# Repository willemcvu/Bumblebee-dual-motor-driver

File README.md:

**_NOTE: Everything here is still actively in development, and is mostly untested. Firmware has not been written; BOMs have not been created. If you'd like to use something here, I would suggest waiting until I have tested all hardware and written firmware._**

**All boards below will be available for sale bare or assembled at some point in the near future, likely on Tindie. For now, feel free to start an issue if you're interested in buying a board.**

Kicad and Arduino sources for the Bumblebee seris of Arduino-compatible dual-motor control boards, all designed to be retrofitable in the Fisher-Price WildThing to provide alternative control means for wheelchair adaption.

There are three different boards, each with discinct purposes.

# Bumblebee-board

This is the main board, and is designed to be a drop-in replacement of the stock WildThing control board. There are two complete H-bridge motor drivers using the A4940 motor driver. The uC is the AtMega328P, with an FTDI USB interface for complete Arduino functionaliy. Connectors for motor and power match those on the stock control board (they mate to standard 1/4" automotive blade terminals), so no crimping or soldering is needed.

Other features include:
* Dual inputs: buttons or joystick
* Choice of JST XH or screw terminals for button/joystick inputs
* On-the-fly configuration via DIP switch
* Potentiometer for speed limiting adjustment
* Built-in fusing
* Fused blade-type 12V and 5V outputs, as well as two extra grounds
* Instructions on the back, as well as Arduino pin equivelancies for the terminal blocks

This board has an operating voltage of 7V-24V, although the max could be raised by changing the 470uF caps to higher-voltage rated caps.

# Bumblebee-adapter

This is probably the ultimate solution for a configurable, low-cost WildThing controller.

This board does not directly drive motors. Instead, it plugs into the joystick headers on the original control board and emulates their signals using two dual-channel SPI DACs. The speed limiting is still controllable via the original button under the seat using this method, and the seat safety switch remains intact.

It does not have onboard USB (due to cost), but has an "FTDI" port for easy programming/configuration with any generic USB-to-serial cable.

It also sports an RJ25 port for joystick input, in addition to a set of 2.54mm holes that can be used either for a terminal block or for a JST XH connector. I'll be designing a 3D-printable joystick unit with a matching RJ25 port at some point in the near future.

# Bumblebee-compact

This very simple board is designed to be a very low-cost, easy-to-solder board that drives external motor controllers, such as RC electronic speed controls (ESCs). All components are through-hole, and the total cost of assembling this should only be around $15.

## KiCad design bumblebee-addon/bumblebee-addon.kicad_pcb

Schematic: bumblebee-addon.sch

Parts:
C1, C2, C3, C4, C5: 0.1u; C_0603_1608Metric
D1: LED; LED_0603_1608Metric
J1: RJ25; RJ12_Amphenol_54601
J2: HEADER; TerminalBlock_TE_282834-4_1x04_P2.54mm_Horizontal
J3: HEADER; TerminalBlock_TE_282834-8_1x08_P2.54mm_Horizontal
J4: ICSP; PinHeader_2x03_P2.54mm_Vertical
J5: FTDI_FLASH; PinSocket_1x06_P2.54mm_Vertical
J6: INTERFACE; JST_XH_B8B-XH-A_1x08_P2.50mm_Vertical
R1: 10k; R_0603_1608Metric
R2: 1k; R_0603_1608Metric
RV1: R_POT_US; Potentiometer_Bourns_PTV09A-1_Single_Vertical
SW1: SW_DIP_x04; SW_DIP_SPSTx04_Slide_6.7x11.72mm_W6.73mm_P2.54mm_LowProfile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
U1: ATmega328P-AU; TQFP-32_7x7mm_P0.8mm
U2, U3: MCP4902; SOIC-14_3.9x8.7mm_P1.27mm

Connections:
+3V3: C1.1, C2.1, C4.1, C5.1, J1.6, J2.1, J4.2, J5.3, J6.1, J6.2, J6.5, R1.1, RV1.3, U1.4 (VCC), U1.6 (VCC), U1.18 (AVCC), U2.1, U2.11, U2.13, U3.1, U3.11, U3.13
/BTN_DN: J3.6, U1.23 (PC0)
/BTN_L: J3.4, U1.27 (PC4)
/BTN_R: J3.2, U1.28 (PC5)
/BTN_UP: J3.8, U1.8 (XTAL2/PB7)
/DAC1_CS: U1.1 (PD3), U2.3
/DAC1_LDAC: U1.2 (PD4), U2.8
/DAC2_CS: U1.9 (PD5), U3.3
/DAC2_LDAC: U1.10 (PD6), U3.8
/FTDI_DTR: C3.1, J5.6
/FTDI_RX: J5.5, U1.31 (PD1)
/FTDI_TX: J5.4, U1.30 (PD0)
/JS_DETECT: J1.5, U1.24 (PC1)
/JS_X: J1.4, J2.2, U1.22 (ADC7)
/JS_Y: J1.3, J2.3, U1.19 (ADC6)
/LED1: D1.2 (A), U1.11 (PD7)
/L_BLACK: J6.3, U2.10
/L_GREEN: J6.4, U2.14
/MISO: J4.1, U1.16 (PB4)
/MOSI: J4.4, U1.15 (PB3), U2.5, U3.5
/RESET: C3.2, J4.5, R1.2, U1.29 (~RESET~/PC6)
/R_BLACK: J6.6, U3.10
/R_GREEN: J6.7, U3.14
/SCK: J4.3, U1.17 (PB5), U2.4, U3.4
GND: C1.2, C2.2, C4.2, C5.2, J1.1, J2.4, J3.1, J3.3, J3.5, J3.7, J4.6, J5.1, J6.8, R2.1, RV1.1, SW1.5, SW1.6, SW1.7, SW1.8, U1.3 (GND), U1.5 (GND), U1.21 (GND), U2.12, U3.12
unnamed: D1.1 (K), R2.2
unnamed: RV1.2, U1.26 (PC3)
unnamed: SW1.1, U1.14 (PB2)
unnamed: SW1.2, U1.13 (PB1)
unnamed: SW1.3, U1.12 (PB0)
unnamed: SW1.4, U1.7 (XTAL1/PB6)

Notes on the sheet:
ICSP
Status LED
Configuration switch
Speed adjust
Controls
Configuration
Fine to program at 5V, as long as it isn't also plugged into the motor driver board.
Output
JS Input
FTDI_PROG

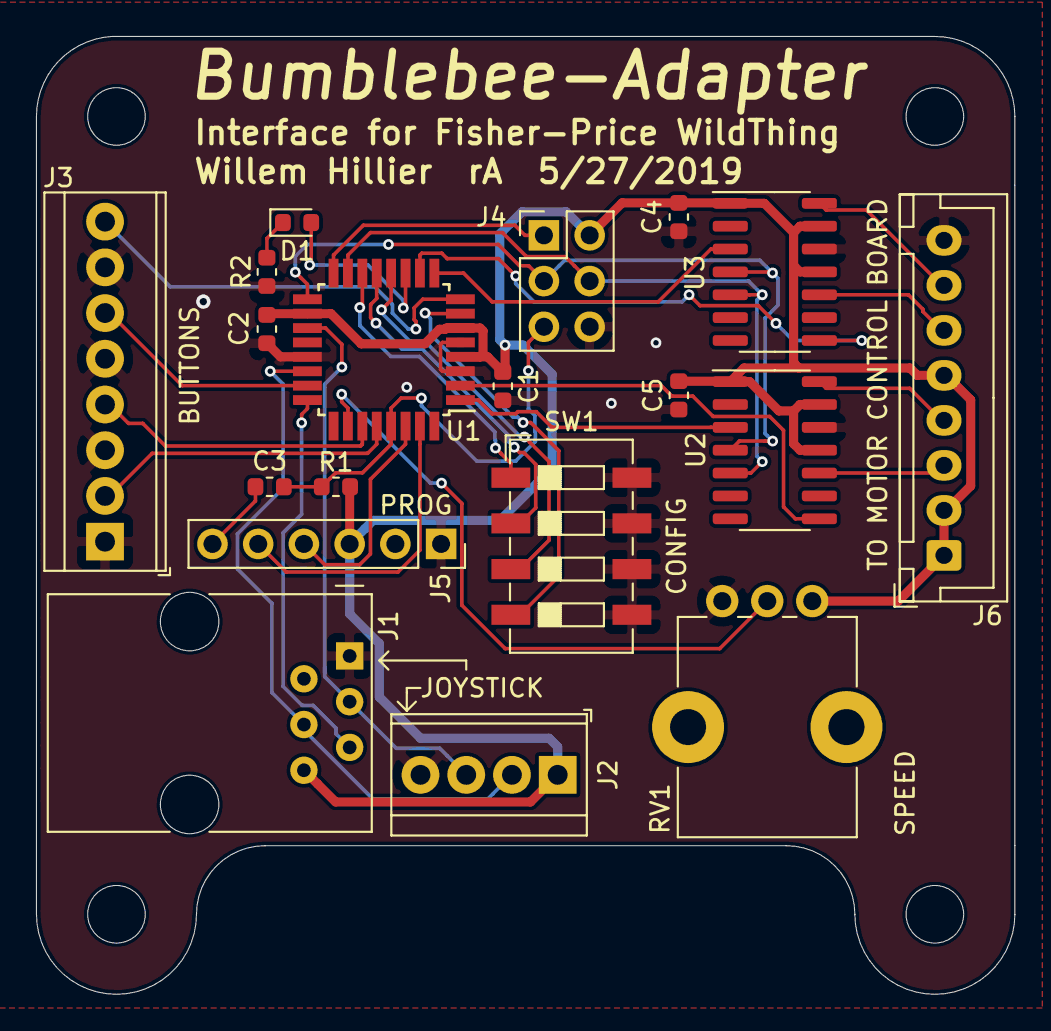
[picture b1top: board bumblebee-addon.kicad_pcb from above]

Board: 2 copper layers, 54.4 x 53.2 mm, 19 parts (0 on the bottom side), 31 nets.

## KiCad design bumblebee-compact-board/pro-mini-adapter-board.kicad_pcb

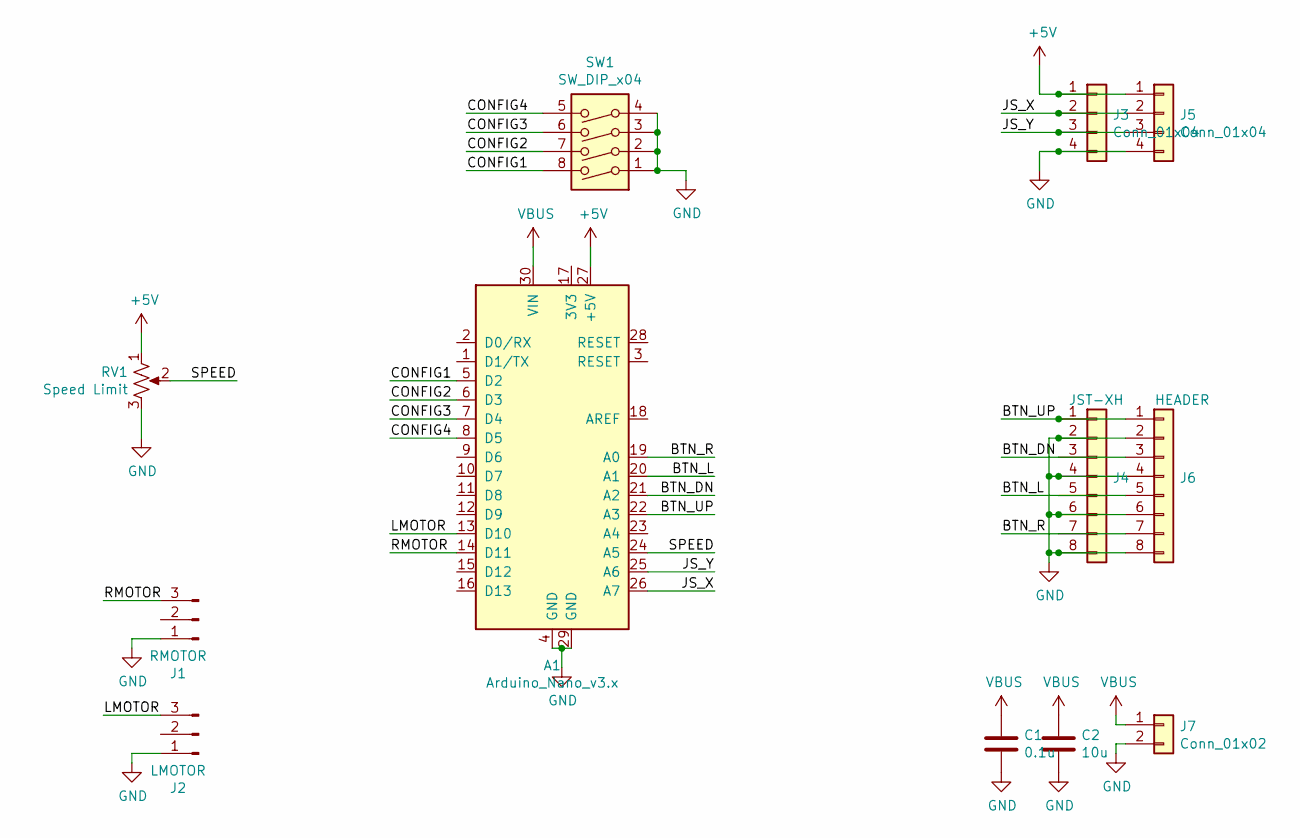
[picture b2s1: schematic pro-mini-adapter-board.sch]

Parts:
A1: Arduino_Nano_v3.x; Arduino_Nano
C1: 0.1u; C_Disc_D5.0mm_W2.5mm_P5.00mm
C2: 10u; C_Radial_D8.0mm_H7.0mm_P3.50mm
J1: RMOTOR; PinHeader_1x03_P2.54mm_Horizontal
J2: LMOTOR; PinHeader_1x03_P2.54mm_Horizontal
J3: Conn_01x04; JST_XH_B4B-XH-A_1x04_P2.50mm_Vertical
J4: JST-XH; JST_XH_B8B-XH-A_1x08_P2.50mm_Vertical
J5: Conn_01x04; TerminalBlock_TE_282834-4_1x04_P2.54mm_Horizontal
J6: HEADER; TerminalBlock_TE_282834-8_1x08_P2.54mm_Horizontal
J7: Conn_01x02; PhoenixContact_MCV_1,5_2-G-5.08_1x02_P5.08mm_Vertical
RV1: Speed Limit; Potentiometer_Bourns_PTV09A-1_Single_Vertical
SW1: SW_DIP_x04; SW_DIP_SPSTx04_Slide_6.7x11.72mm_W7.62mm_P2.54mm_LowProfile

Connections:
+5V: A1.27 (+5V), J3.1, J5.1, RV1.1
/BTN_DN: A1.21 (A2), J4.3, J6.3
/BTN_L: A1.20 (A1), J4.5, J6.5
/BTN_R: A1.19 (A0), J4.7, J6.7
/BTN_UP: A1.22 (A3), J4.1, J6.1
/CONFIG1: A1.5 (D2), SW1.8
/CONFIG2: A1.6 (D3), SW1.7
/CONFIG3: A1.7 (D4), SW1.6
/CONFIG4: A1.8 (D5), SW1.5
/JS_X: A1.26 (A7), J3.2, J5.2
/JS_Y: A1.25 (A6), J3.3, J5.3
/LMOTOR: A1.13 (D10), J2.3
/RMOTOR: A1.14 (D11), J1.3
/SPEED: A1.24 (A5), RV1.2
GND: A1.4 (GND), A1.29 (GND), C1.2, C2.2, J1.1, J2.1, J3.4, J4.2, J4.4, J4.6, J4.8, J5.4, J6.2, J6.4, J6.6, J6.8, J7.2, RV1.3, SW1.1, SW1.2, SW1.3, SW1.4
VBUS: A1.30 (VIN), C1.1, C2.1, J7.1

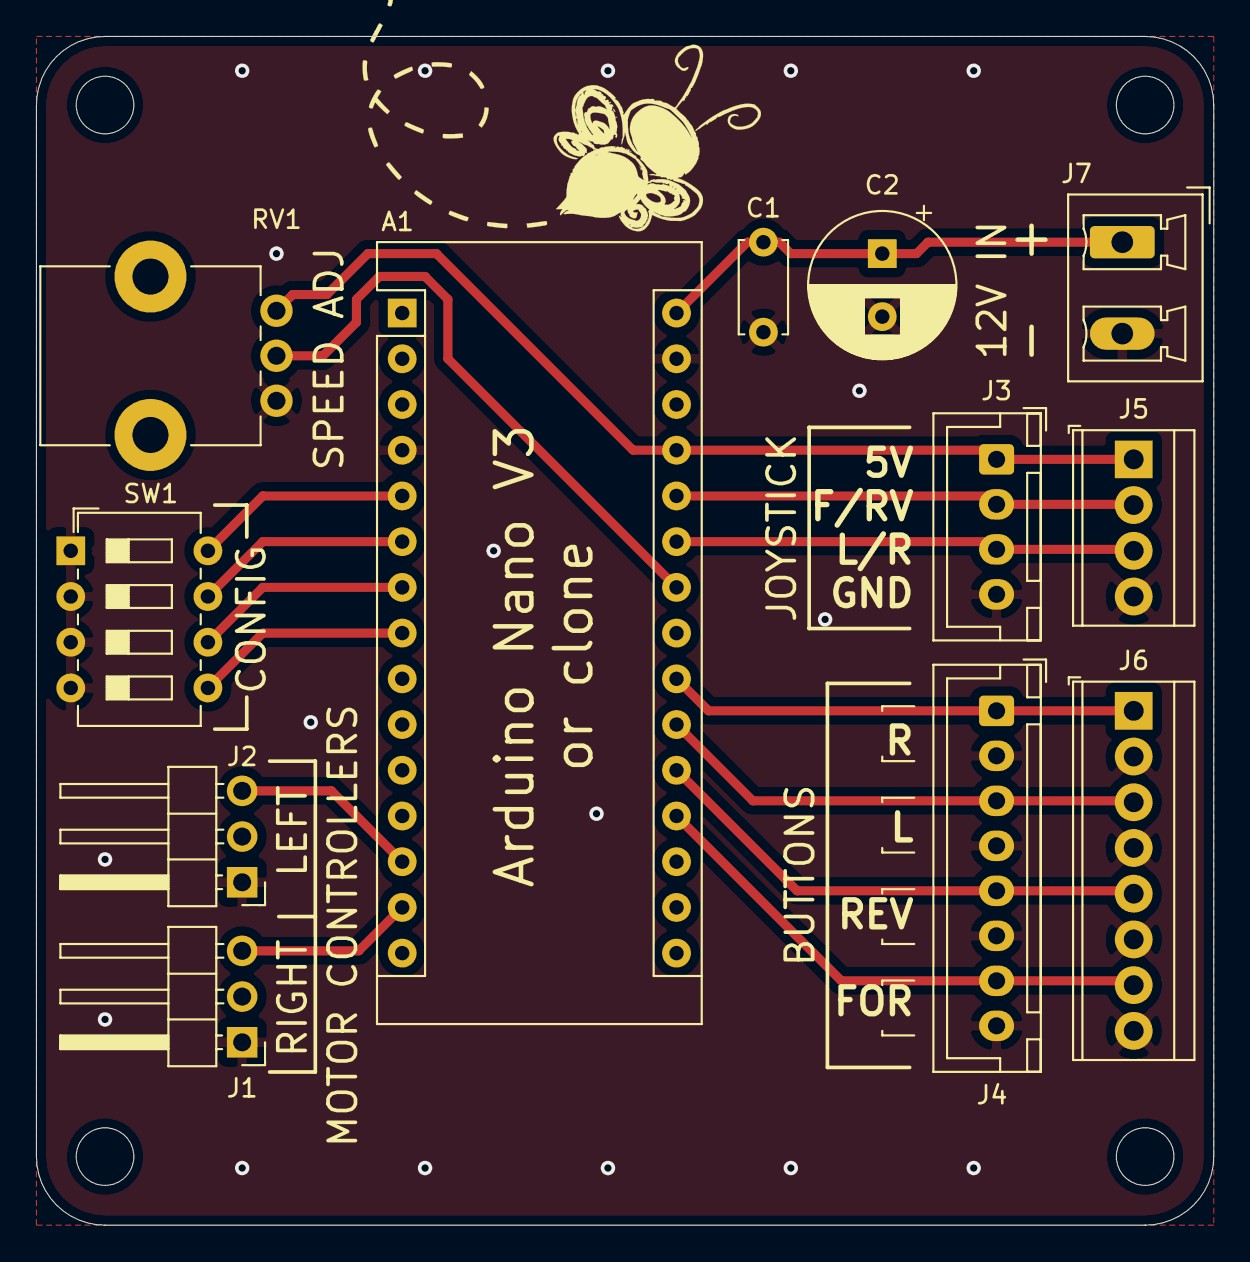
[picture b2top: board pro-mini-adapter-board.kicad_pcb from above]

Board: 2 copper layers, 65.4 x 66.0 mm, 12 parts (0 on the bottom side), 16 nets.

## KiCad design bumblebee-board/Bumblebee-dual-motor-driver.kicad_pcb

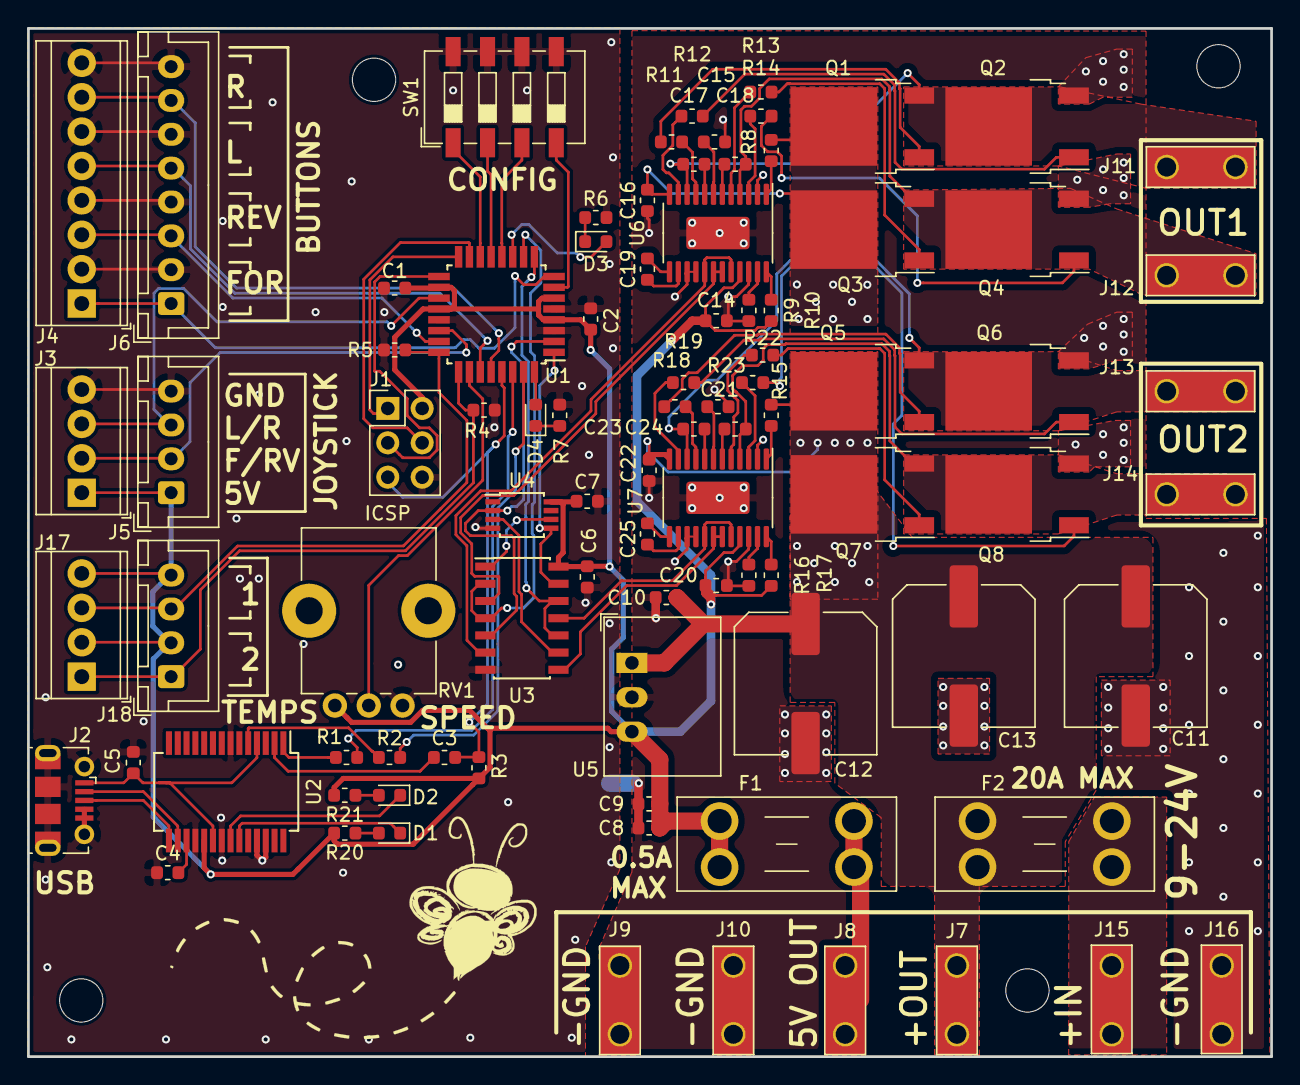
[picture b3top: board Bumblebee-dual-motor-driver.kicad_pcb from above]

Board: 2 copper layers, 91.8 x 75.9 mm, 90 parts (1 on the bottom side), 85 nets.

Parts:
C1, C2, C3, C4, C5, C6, C7, C9, C10, C14, C16, C20, C22: 0.1u; C_0603_1608Metric
C8, C15, C21: 10u; C_0603_1608Metric
C11, C12, C13: 470u; C_Elec_10x10.2
C17, C18, C19, C23, C24, C25: 1u; C_0603_1608Metric
D1: RX; LED_0603_1608Metric
D2: TX; LED_0603_1608Metric
D3, D4: LED; LED_0603_1608Metric
F1: 0.5A; Fuseholder_Blade_Mini_Keystone_3568
F2: 20A; Fuseholder_Blade_Mini_Keystone_3568
J1: ICSP; PinHeader_2x03_P2.54mm_Vertical
J2: USB_B_Micro; USB_Micro-B_Molex-105017-0001
J3, J17: HEADER; TerminalBlock_TE_282834-4_1x04_P2.54mm_Horizontal
J4: HEADER; TerminalBlock_TE_282834-8_1x08_P2.54mm_Horizontal
J5, J18: JST-XH; JST_XH_B4B-XH-A_1x04_P2.50mm_Vertical
J6: JST-XH; JST_XH_B8B-XH-A_1x08_P2.50mm_Vertical
J7: 12V_OUT; TE_1217861-1
J8: 5V_OUT; TE_1217861-1
J9, J10: GND; TE_1217861-1
J11: MOTOR1_A; TE_1217861-1
J12: MOTOR1_B; TE_1217861-1
J13: MOTOR2_A; TE_1217861-1
J14: MOTOR2_B; TE_1217861-1
J15: MAIN+; TE_1217861-1
J16: MAIN-; TE_1217861-1
Q1, Q2, Q3, Q4, Q5, Q6, Q7, Q8: Q_NMOS_GDS; TO-252-2
R1, R2, R6, R7, R20, R21: 1k; R_0603_1608Metric
R3, R4, R5, R9, R16: 10k; R_0603_1608Metric
R8, R15: 27k; R_0603_1608Metric
R10, R17: 82k; R_0603_1608Metric
R11, R12, R13, R14, R18, R19, R22, R23: 27; R_0603_1608Metric
RV1: R_POT_US; Potentiometer_Bourns_PTV09A-1_Single_Vertical
SW1: SW_DIP_x04; dipLOGO
SW1#2: SW_DIP_x04; SW_DIP_SPSTx04_Slide_6.7x11.72mm_W6.73mm_P2.54mm_LowProfile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
U1: ATmega328P-AU; TQFP-32_7x7mm_P0.8mm
U2: FT232RL; SSOP-28_5.3x10.2mm_P0.65mm
U3: 74LS08; SOIC-14_3.9x8.7mm_P1.27mm
U4: 74LVC2G240; TSSOP-8_3x3mm_P0.65mm
U5: R-78E5.0-0.5; Converter_DCDC_RECOM_R-78E-0.5_THT
U6, U7: A4940KLPTR-T; HTSSOP-24-1EP_4.4x7.8mm_P0.65mm_EP3.4x7.8mm_Mask2.4x4.68mm

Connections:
+5V: C1.1, C2.1, C6.1, C7.1, C8.1, C9.1, C14.1, C20.1, F1.1, J1.2, J3.1, J5.1, J17.2, J17.4, J18.2, J18.4, R3.1, R9.1, R16.1, R20.2, R21.2, RV1.3, U1.4, U1.6, U1.18, U1.20, U2.19, U3.14, U4.8, U5.3, U6.21, U7.21
/BTN_DN: J4.3, J6.3, U1.23
/BTN_L: J4.5, J6.5, U1.27
/BTN_R: J4.7, J6.7, U1.28
/BTN_UP: J4.1, J6.1, U1.8
/JS_X: J3.2, J5.2, U1.22
/JS_Y: J3.3, J5.3, U1.19
/LED1: D3.2, U1.11
/LED2: D4.2, U1.32
/M8RXD: R1.2, U1.30
/M8TXD: R2.2, U1.31
/MISO: J1.1, U1.16
/MOSI: J1.4, U1.15
/MOTOR1_A: C17.1, J11.1, Q1.3, Q2.2, U6.10
/MOTOR1_B: C18.1, J12.1, Q3.3, Q4.2, U6.4
/MOTOR1_DIR: U1.2, U3.5, U4.2
/MOTOR1_DRIVER/AHI: U3.6, U6.17, U6.20
/MOTOR1_DRIVER/ALO: U3.3, U6.18, U6.19
/MOTOR1_DRIVER/~FAULT: R9.2, U6.24
/MOTOR1_DRIVER/~RESET: R8.1, U6.1
/MOTOR1_PWM: U1.10, U3.2, U3.4
/MOTOR2_A: C23.1, J13.1, Q5.3, Q6.2, U7.10
/MOTOR2_B: C24.1, J14.1, Q7.3, Q8.2, U7.4
/MOTOR2_DIR: U1.1, U3.13, U4.5
/MOTOR2_DRIVER/AHI: U3.11, U7.17, U7.20
/MOTOR2_DRIVER/ALO: U3.8, U7.18, U7.19
/MOTOR2_DRIVER/~FAULT: R16.2, U7.24
/MOTOR2_DRIVER/~RESET: R15.1, U7.1
/MOTOR2_PWM: U1.9, U3.10, U3.12
/NTC1: J17.1, J18.1, R4.2, U1.25
/NTC2: J17.3, J18.3, R5.2, U1.24
/RESET: C3.2, J1.5, R3.2, U1.29
/SCK: J1.3, U1.17
/USB_PWR: C5.1, J2.1, U2.4, U2.20
GND: C1.2, C2.2, C4.1, C5.2, C6.2, C7.2, C8.2, C9.2, C10.2, C11.2, C12.2, C13.2, C14.2, C15.2, C16.1, C20.2, C21.2, C22.1, J1.6, J2.4, J2.5, J2.6, J3.4, J4.2, J4.4, J4.6, J4.8, J5.4, J6.2, J6.4, J6.6, J6.8, J9.1, J10.1, J16.1, Q2.3, Q4.3, Q6.3, Q8.3, R4.1, R5.1, R6.1, R7.1, R10.2, R17.2, RV1.1, SW1#2.5, SW1#2.6, SW1#2.7, SW1#2.8, U1.3, U1.5, U1.21, U2.7, U2.18, U2.21, U2.25, U2.26, U3.7, U4.4, U5.2, U6.2, U6.15, U6.16, U6.22, U6.25, U7.2, U7.15, U7.16, U7.22, U7.25
unnamed: C3.1, U2.2
unnamed: C4.2, U2.17
unnamed: C15.1, U6.7
unnamed: C17.2, U6.8
unnamed: C18.2, U6.6
unnamed: C19.1, U6.14
unnamed: C19.2, U6.13
unnamed: C21.1, U7.7
unnamed: C23.2, U7.8
unnamed: C24.2, U7.6
unnamed: C25.1, U7.14
unnamed: C25.2, U7.13
unnamed: D1.1, U2.23
unnamed: D1.2, R20.1
unnamed: D2.1, U2.22
unnamed: D2.2, R21.1
unnamed: D3.1, R6.2
unnamed: D4.1, R7.2
unnamed: F1.2, J8.1
unnamed: F2.2, J15.1
unnamed: J2.2, U2.16
unnamed: J2.3, U2.15
unnamed: Q1.1, R11.1
unnamed: Q2.1, R12.1
unnamed: Q3.1, R13.1
unnamed: Q4.1, R14.1
unnamed: Q5.1, R18.1
unnamed: Q6.1, R19.1
unnamed: Q7.1, R22.1
unnamed: Q8.1, R23.1
unnamed: R1.1, U2.1
unnamed: R2.1, U2.5
unnamed: R10.1, U6.23
unnamed: R11.2, U6.9
unnamed: R12.2, U6.11
unnamed: R13.2, U6.5
unnamed: R14.2, U6.3
unnamed: R17.1, U7.23
unnamed: R18.2, U7.9
unnamed: R19.2, U7.11
unnamed: R22.2, U7.5
unnamed: R23.2, U7.3
unnamed: RV1.2, U1.26
unnamed: SW1#2.1, U1.14
unnamed: SW1#2.2, U1.13
unnamed: SW1#2.3, U1.12
unnamed: SW1#2.4, U1.7
unnamed: U3.1, U4.6
unnamed: U3.9, U4.3
VBUS: C10.1, C11.1, C12.1, C13.1, C16.2, C22.2, F2.1, J7.1, Q1.2, Q3.2, Q5.2, Q7.2, R8.2, R15.2, U5.1, U6.12, U7.12

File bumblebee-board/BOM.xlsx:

Id | Designator | Package | Quantity | Designation | Manufacturer | PN
4 | J11 | TE_1217861-1 | 9 | MOTOR1_A | TE | 1217861-1
6 | C13,C11,C12 | C_Elec_10x10.2 | 3 | 470u |  | EEV477M025S9PAA
7 | C24,C25,C23,C17,C18,C19 | C_0603_1608Metric | 6 | 1u | NIC Components | NMC0603Y5V105Z16TRPF
8 | C22,C20,C1,C2,C3,C4,C5,C6,C7,C9,C10,C14,C16 | C_0603_1608Metric | 13 | 0.1u
9 | C21,C8,C15 | C_0603_1608Metric | 3 | 10u
10 | R19,R18,R16,R17,R10,R11,R12,R13 | R_0603_1608Metric | 8 | 27 | NIC Components | NRC06F27R0TRF
11 | U7,U6 | HTSSOP-24-1EP_4.4x7.8mm_P0.65mm_EP3.4x7.8mm_Mask2.4x4.68mm | 2 | A4940KLPTR-T | ALLEGRO | A4940KLPTR-T
12 | Q7,Q6,Q5,Q8,Q1,Q2,Q3,Q4 | TO-252-2 | 8 | Q_NMOS_GDS | Infineon | IRFR3410TRLPBF
15 | R14,R3,R4,R5,R8 | R_0603_1608Metric | 5 | 10k
16 | R15,R9 | R_0603_1608Metric | 2 | 82k | NIC Components | NRC06J823TRF
17 | D1 | LED_0603_1608Metric | 1 | RX
18 | D2 | LED_0603_1608Metric | 1 | TX
19 | D3,D4 | LED_0603_1608Metric | 2 | LED
20 | J5,J18 | JST_XH_B4B-XH-A_1x04_P2.50mm_Vertical | 2 | JST-XH
21 | J6 | JST_XH_B8B-XH-A_1x08_P2.50mm_Vertical | 1 | JST-XH
28 | R1,R2,R6,R7,R20,R21 | R_0603_1608Metric | 6 | 1k
29 | SW1 | SW_DIP_SPSTx04_Slide_6.7x11.72mm_W6.73mm_P2.54mm_LowProfile_Jpin | 1 | SW_DIP_x04 | CTS | 219-4LPST
30 | U1 | TQFP-32_7x7mm_P0.8mm | 1 | ATmega328P-AU
31 | U2 | SSOP-28_5.3x10.2mm_P0.65mm | 1 | FT232RL | FTDI | FT232RL-TUBE
32 | U3 | SOIC-14_3.9x8.7mm_P1.27mm | 1 | 74LS08 | Texas Instruments | SN74LS08D
33 | U4 | TSSOP-8_3x3mm_P0.65mm | 1 | 74LVC2G240 | Nexperia | 74LVC2G240DC,125
34 | U5 | Converter_DCDC_RECOM_R-78E-0.5_THT | 1 | R-78E5.0-0.5 | Recom | R-78E5.0-0.5
35 | J1 | PinHeader_2x03_P2.54mm_Vertical | 1 | ICSP
36 | F1,F2 | Fuseholder_Blade_Mini_Keystone_3568 | 2 | 0.5A
38 | J4 | TerminalBlock_TE_282834-8_1x08_P2.54mm_Horizontal | 1 | HEADER
39 | J3,J17 | TerminalBlock_TE_282834-4_1x04_P2.54mm_Horizontal | 2 | HEADER
40 | J2 | USB_Micro-B_Molex-105017-0001 | 1 | USB_B_Micro | Molex | 105017-0001
41 | RV1 | Potentiometer_Bourns_PTV09A-1_Single_Vertical | 1 | R_POT_US | Bourns | PTV09A-4020F-B103

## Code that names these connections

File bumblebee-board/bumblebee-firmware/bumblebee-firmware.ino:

#define MOTOR1_DIR 4
#define MOTOR1_PWM 3
#define MOTOR2_DIR 6
#define MOTOR2_PWM 5

#define LOOP_DELAY 32
void setup() {
  //PWM frequency set up
  //TCCR2B = TCCR2B & B11111000 | B00000010; // D3 and D11, for PWM frequency of 3921.16 Hz
  //TCCR0B = TCCR0B & B11111000 | B00000010; // D5 and D6, for PWM frequency of 7812.50 Hz

  //Outputs
  pinMode(MOTOR1_DIR,OUTPUT);
  pinMode(MOTOR1_PWM,OUTPUT);
  pinMode(MOTOR2_DIR,OUTPUT);
  pinMode(MOTOR2_PWM,OUTPUT);
}

void loop() {
  //Test ramp motor forward/backwards
  
   digitalWrite(MOTOR2_DIR,1);

  //ramp up
  for(int i=0;i<256;i=i+LOOP_DELAY){
    analogWrite(MOTOR2_PWM,i);
    delay(100);
  }

  //ramp down
  for(int i=256;i>0;i=i-LOOP_DELAY){
    analogWrite(MOTOR2_PWM,i);
    delay(100);
  }

  //backwards
  digitalWrite(MOTOR2_DIR,0);

  //ramp up
  for(int i=0;i<256;i=i+LOOP_DELAY){
    analogWrite(MOTOR2_PWM,i);
    delay(100);
  }

  //ramp down
  for(int i=256;i>0;i=i-LOOP_DELAY){
    analogWrite(MOTOR2_PWM,i);
    delay(100);
  }


}

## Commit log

2019-05-08 Schematics fully drawn.
2019-05-08 Assigned all footprints.
    Still need to pick and check FET footprint, pick pot.
2019-05-08 Started moving components around on PCB.
2019-05-08 Fixed small issues and started laying out H-bridge
2019-05-08 Layed out single H-bridge, started copying to the other H-bridge
2019-05-09 Further progress laying out Bumblebee
2019-05-09 Finished routing board. Need to still do documentation.
2019-05-10 Done with silkscreen
    TODO: Add keepout areas on high-current traces
2019-05-11 Made bumblebee-compact. Added VT logo to both. Made gerbers. Shipping.
2019-05-12 Created initial BOM
2019-05-27 Started work on bumblebee-addon
2019-05-27 Bumblebee-board r2 ready to ship.
2019-05-27 Shipped new revs of all boards.
2019-05-27 Added board images, cleaned up.
2019-05-28 Renamed all files to bumblebee-adapter
